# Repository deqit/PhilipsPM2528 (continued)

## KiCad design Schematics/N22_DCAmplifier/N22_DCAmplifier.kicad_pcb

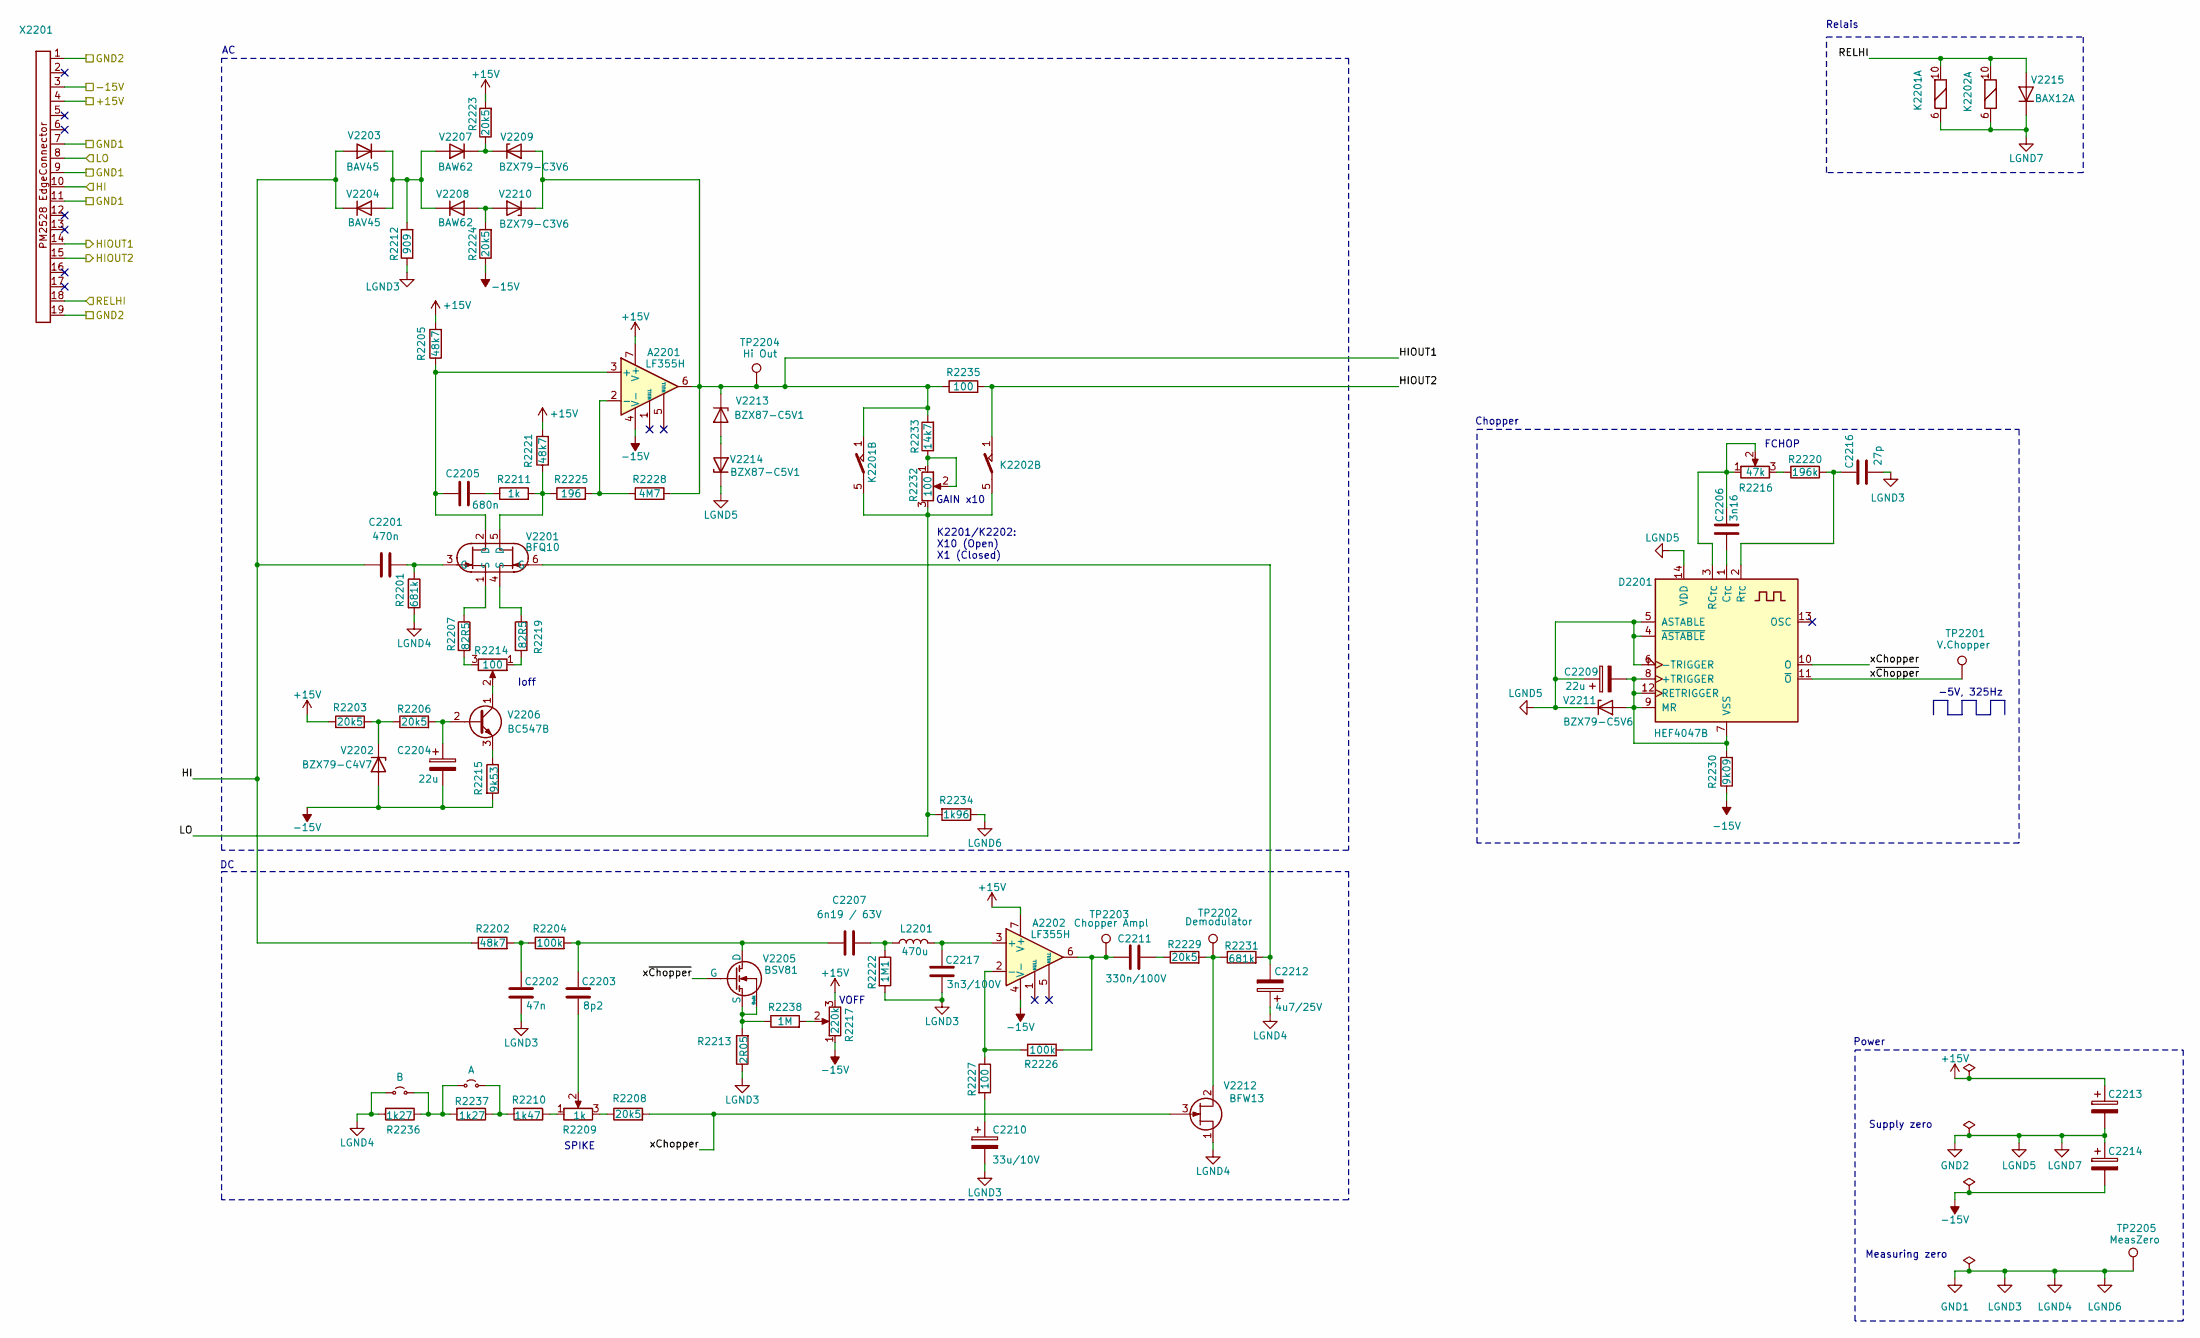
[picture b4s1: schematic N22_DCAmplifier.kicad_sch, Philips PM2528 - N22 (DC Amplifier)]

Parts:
A2201, A2202: LF355H; DIP-8_W7.62mm
C2201: 470n; C_Rect_L18.0mm_W6.0mm_P15.00mm_FKS3_FKP3
C2202: 47n; C_Rect_L10.0mm_W4.0mm_P7.50mm_FKS3_FKP3
C2203: 8p2; C_Disc_D4.3mm_W1.9mm_P5.00mm
C2204, C2209: 22u; CP_Radial_Tantal_D4.5mm_P5.00mm
C2205: 680n; C_Rect_L18.0mm_W5.0mm_P15.00mm_FKS3_FKP3
C2206: 3n16; C_Axial_L3.8mm_D2.6mm_P15.00mm_Horizontal
C2207: 6n19 / 63V; C_Axial_L3.8mm_D2.6mm_P15.00mm_Horizontal
C2210: 33u/10V; CP_Radial_Tantal_D4.5mm_P5.00mm
C2211: 330n/100V; C_Rect_L18.0mm_W5.0mm_P15.00mm_FKS3_FKP3
C2212: 4u7/25V; CP_Radial_Tantal_D4.5mm_P5.00mm
C2213, C2214: 6u8; CP_Radial_Tantal_D4.5mm_P5.00mm
C2216: 27p; C_Disc_D5.1mm_W3.2mm_P5.00mm
C2217: 3n3/100V; C_Disc_D4.3mm_W1.9mm_P5.00mm
D2201: HEF4047B; DIP-14_W7.62mm
JP2201: A; TestPoint_Bridge_Pitch5.08mm_Drill0.7mm
JP2202: B; TestPoint_Bridge_Pitch5.08mm_Drill0.7mm
K2201, K2202: Reed relay assy
L2201: 470u; L_Axial_L9.5mm_D4.0mm_P15.24mm_Horizontal_Fastron_SMCC
R2201, R2231: 681k; R_Axial_DIN0207_L6.3mm_D2.5mm_P10.16mm_Horizontal
R2202, R2205, R2221: 48k7; R_Axial_DIN0207_L6.3mm_D2.5mm_P10.16mm_Horizontal
R2203, R2206, R2208, R2223, R2224, R2229: 20k5; R_Axial_DIN0207_L6.3mm_D2.5mm_P10.16mm_Horizontal
R2204, R2226: 100k; R_Axial_DIN0207_L6.3mm_D2.5mm_P10.16mm_Horizontal
R2207, R2219: 82R5; R_Axial_DIN0207_L6.3mm_D2.5mm_P10.16mm_Horizontal
R2209: 1k; Trimmer vertical
R2210: 1k47; R_Axial_DIN0207_L6.3mm_D2.5mm_P10.16mm_Horizontal
R2211: 1k; R_Axial_DIN0207_L6.3mm_D2.5mm_P10.16mm_Horizontal
R2212: 909; R_Axial_DIN0207_L6.3mm_D2.5mm_P10.16mm_Horizontal
R2213: 2R05; R_Axial_DIN0207_L6.3mm_D2.5mm_P10.16mm_Horizontal
R2214, R2232: 100; Trimmer vertical
R2215: 9k53; R_Axial_DIN0207_L6.3mm_D2.5mm_P10.16mm_Horizontal
R2216: 47k; Trimmer vertical
R2217: 220k; Trimmer vertical
R2220: 196k; R_Axial_DIN0207_L6.3mm_D2.5mm_P10.16mm_Horizontal
R2222: 1M1; R_Axial_DIN0207_L6.3mm_D2.5mm_P10.16mm_Horizontal
R2225: 196; R_Axial_DIN0207_L6.3mm_D2.5mm_P10.16mm_Horizontal
R2227, R2235: 100; R_Axial_DIN0207_L6.3mm_D2.5mm_P10.16mm_Horizontal
R2228: 4M7; R_Axial_DIN0207_L6.3mm_D2.5mm_P10.16mm_Horizontal
R2230: 9k09; R_Axial_DIN0207_L6.3mm_D2.5mm_P10.16mm_Horizontal
R2233: 14k7; R_Axial_DIN0207_L6.3mm_D2.5mm_P10.16mm_Horizontal
R2234: 1k96; R_Axial_DIN0207_L6.3mm_D2.5mm_P10.16mm_Horizontal
R2236, R2237: 1k27; R_Axial_DIN0207_L6.3mm_D2.5mm_P10.16mm_Horizontal
R2238: 1M; R_Axial_DIN0309_L9.0mm_D3.2mm_P15.24mm_Horizontal
TP2201: V.Chopper; Pin_D0.9mm_L10.0mm_W2.4mm_FlatFork
TP2202: Demodulator; Pin_D0.9mm_L10.0mm_W2.4mm_FlatFork
TP2203: Chopper Ampl; Pin_D0.9mm_L10.0mm_W2.4mm_FlatFork
TP2204: Hi Out; Pin_D0.9mm_L10.0mm_W2.4mm_FlatFork
TP2205: MeasZero; Pin_D0.9mm_L10.0mm_W2.4mm_FlatFork
V2201: BFQ10; TO-75-6
V2202: BZX79-C4V7; D_DO-35_SOD27_P10.16mm_Horizontal
V2203, V2204: BAV45; BAV45_TO-18-2
V2205: BSV81; TO-72-4
V2206: BC547B; TO-92_Inline
V2207, V2208: BAW62; D_DO-35_SOD27_P10.16mm_Horizontal
V2209, V2210: BZX79-C3V6; D_DO-35_SOD27_P10.16mm_Horizontal
V2211: BZX79-C5V6; D_DO-35_SOD27_P10.16mm_Horizontal
V2212: BFW13; TO-72-4
V2213, V2214: BZX87-C5V1; D_DO-35_SOD27_P12.70mm_Horizontal
V2215: BAX12A; D_DO-34_SOD68_P10.16mm_Horizontal
X2201: PM2528Edgeconnector

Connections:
+15V: A2201.7 (V+), A2202.7 (V+), C2213.1, R2203.1, R2205.2, R2217.3, R2221.2, R2223.2, X2201.4
-15V: A2201.4 (V-), A2202.4 (V-), C2204.2, C2214.2, R2215.2, R2217.1, R2224.1, R2230.1, V2202.2 (A), X2201.3
/HI: C2201.1, R2202.1, V2203.2 (A), V2204.1 (K), X2201.10
/HIOUT1: A2201.6, K2201.1, R2228.2, R2233.2, R2235.1, TP2204.1 (1_1), V2209.2 (A), V2210.1 (K), V2213.1 (K), X2201.14
/HIOUT2: K2202.1, R2235.2, X2201.15
/LO: K2201.5, K2202.5, R2232.3, R2234.2, X2201.8
/RELHI: K2201.10, K2202.10, V2215.2 (A), X2201.18
/xChopper: D2201.10 (O), R2208.2, V2212.3 (G)
/x~Chopper: D2201.11 (~O), TP2201.1 (1_1), V2205.2 (G)
GND1: C2202.1, C2210.2, C2212.1, C2216.2, C2217.1, JP2202.1 (A_1), R2201.2, R2212.1, R2213.1, R2222.2, R2234.1, R2236.2, TP2205.1 (1_1), V2212.1 (S), X2201.7, X2201.9, X2201.11
GND2: C2209.1, C2213.2, C2214.1, D2201.4 (~ASTABLE), D2201.5 (ASTABLE), D2201.6 (-TRIGGER), D2201.14 (VDD), K2201.6, K2202.6, V2211.1 (K), V2214.1 (K), V2215.1 (K), X2201.1, X2201.19
unnamed: A2201.3 (+), C2205.1, R2205.1, V2201.2 (D)
unnamed: A2201.2 (-), R2225.2, R2228.1
unnamed: A2202.3 (+), C2217.2, L2201.2
unnamed: A2202.2 (-), R2226.1, R2227.1
unnamed: A2202.6, C2211.1, R2226.2, TP2203.1 (1_1)
unnamed: C2201.2, R2201.1, V2201.3 (G)
unnamed: C2202.2, R2202.2, R2204.1
unnamed: C2203.1, R2209.2
unnamed: C2205.2, R2211.1
unnamed: C2207.2, L2201.1, R2222.1
unnamed: C2210.1, R2227.2
unnamed: C2211.2, R2229.1
unnamed: C2212.2, R2231.2, V2201.6 (G)
unnamed: C2209.2, D2201.7 (VSS), D2201.8 (+TRIGGER), D2201.9 (MR), D2201.12 (RETRIGGER), R2230.2, V2211.2 (A)
unnamed: C2206.1, D2201.1 (C_{TC})
unnamed: C2206.2, D2201.3 (RC_{TC}), R2216.1, R2216.2
unnamed: C2216.1, D2201.2 (R_{TC}), R2220.1
unnamed: JP2201.1 (A_1), JP2202.2 (B), R2236.1, R2237.2
unnamed: JP2201.2 (B), R2210.2, R2237.1
unnamed: R2207.1, V2201.1 (S)
unnamed: R2207.2, R2214.3
unnamed: R2208.1, R2209.3
unnamed: R2209.1, R2210.1
unnamed: R2211.2, R2221.1, R2225.1, V2201.5 (D)
unnamed: R2214.1, R2219.2
unnamed: R2216.3, R2220.2
unnamed: R2217.2, R2238.2
unnamed: R2219.1, V2201.4 (S)
unnamed: R2232.1, R2232.2, R2233.1
unnamed: R2203.2, R2206.1, V2202.1 (K)
unnamed: R2212.2, V2203.1 (K), V2204.2 (A), V2207.2 (A), V2208.1 (K)
unnamed: R2213.2, R2238.1, V2205.3 (S), V2205.4 (Bulk)
unnamed: C2203.2, C2207.1, R2204.2, V2205.1 (D)
unnamed: C2204.1, R2206.2, V2206.2 (B)
unnamed: R2214.2, V2206.1 (C)
unnamed: R2215.1, V2206.3 (E)
unnamed: R2223.1, V2207.1 (K), V2209.1 (K)
unnamed: R2224.2, V2208.2 (A), V2210.2 (A)
unnamed: R2229.2, R2231.1, TP2202.1 (1_1), V2212.2 (D)
unnamed: V2213.2 (A), V2214.2 (A)

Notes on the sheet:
Relais
SPIKE
Supply zero
GAIN x10
K2201/K2202: X10 (Open) X1 (Closed)
VOFF
Chopper
-5V, 325Hz
FCHOP
Power
Measuring zero
Ioff

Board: 2 copper layers, 81 parts (0 on the bottom side), 51 nets, no tracks yet.

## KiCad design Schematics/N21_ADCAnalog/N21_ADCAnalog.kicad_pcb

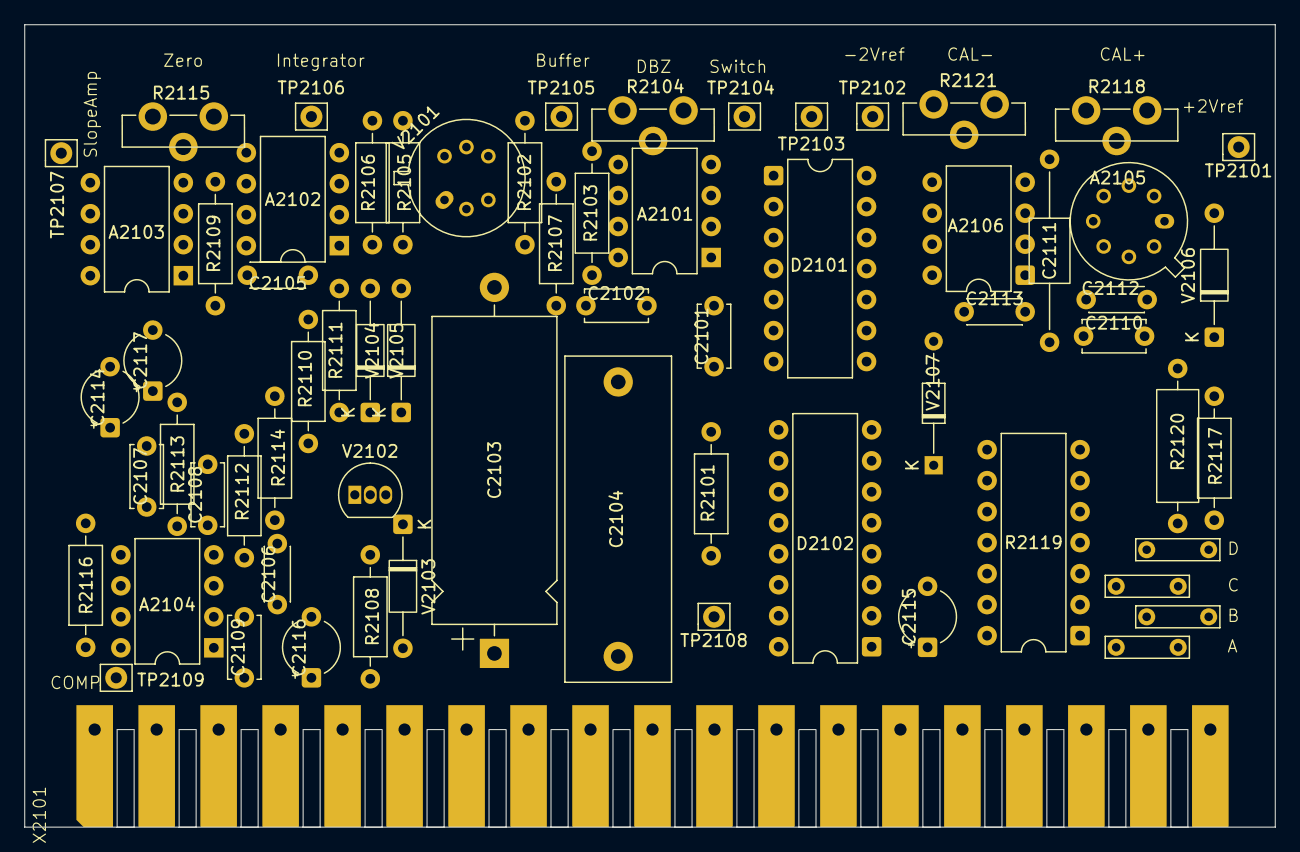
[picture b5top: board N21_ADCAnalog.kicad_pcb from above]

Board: 2 copper layers, 102.5 x 65.8 mm, 67 parts (0 on the bottom side), 54 nets, no tracks yet.

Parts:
A2101: LF356H; DIP-8_W7.62mm
A2102, A2106: LM201AN; DIP-8_W7.62mm
A2103: LF355H; DIP-8_W7.62mm
A2104: LM311N; DIP-8_W7.62mm
A2105: LM208AH; TO-99-8
C2101, C2102: 10n; C_Disc_D5.0mm_W2.5mm_P5.00mm
C2103: 162n; CP_Axial_L25.0mm_D10.0mm_P30.00mm_Horizontal
C2104: 3u3; C_Rect_L26.5mm_W8.5mm_P22.50mm_MKS4
C2105: 33p/100V; C_Disc_D4.3mm_W1.9mm_P5.00mm
C2106: 220p/500V; C_Disc_D4.3mm_W1.9mm_P5.00mm
C2107, C2108, C2109: 22n; C_Disc_D5.0mm_W2.5mm_P5.00mm
C2110: 4n7; C_Disc_D5.0mm_W2.5mm_P5.00mm
C2111: 4n22; C_Axial_L5.1mm_D3.1mm_P15.00mm_Horizontal
C2112, C2113: 33p; C_Disc_D4.3mm_W1.9mm_P5.00mm
C2114, C2117: 6u8; CP_Radial_Tantal_D4.5mm_P5.00mm
C2115: 22u/10V; CP_Radial_Tantal_D4.5mm_P5.00mm
C2116: 22u; CP_Radial_Tantal_D4.5mm_P5.00mm
D2101: HEF4066B; DIP-14_W7.62mm
D2102: HEF4104B; DIP-16_W7.62mm
JP2101: A; TestPoint_Bridge_Pitch5.08mm_Drill0.7mm
JP2102: B; TestPoint_Bridge_Pitch5.08mm_Drill0.7mm
JP2103: C; TestPoint_Bridge_Pitch5.08mm_Drill0.7mm
JP2104: D; TestPoint_Bridge_Pitch5.08mm_Drill0.7mm
R2101: 8k66; R_Axial_DIN0207_L6.3mm_D2.5mm_P10.16mm_Horizontal
R2102: 140k; R_Axial_DIN0207_L6.3mm_D2.5mm_P10.16mm_Horizontal
R2103: 64k9; R_Axial_DIN0207_L6.3mm_D2.5mm_P10.16mm_Horizontal
R2104: 680k; Trimmer vertical
R2105, R2106: 21M1; R_Axial_DIN0207_L6.3mm_D2.5mm_P10.16mm_Horizontal
R2107: 24k9; R_Axial_DIN0207_L6.3mm_D2.5mm_P10.16mm_Horizontal
R2108: 40k2; R_Axial_DIN0207_L6.3mm_D2.5mm_P10.16mm_Horizontal
R2109: 5k9; R_Axial_DIN0207_L6.3mm_D2.5mm_P10.16mm_Horizontal
R2110: 121k; R_Axial_DIN0207_L6.3mm_D2.5mm_P10.16mm_Horizontal
R2111: 5k90; R_Axial_DIN0207_L6.3mm_D2.5mm_P10.16mm_Horizontal
R2112, R2113: 442; R_Axial_DIN0207_L6.3mm_D2.5mm_P10.16mm_Horizontal
R2114: 442k; R_Axial_DIN0207_L6.3mm_D2.5mm_P10.16mm_Horizontal
R2115: 47k; Trimmer vertical
R2116: 1k05; R_Axial_DIN0207_L6.3mm_D2.5mm_P10.16mm_Horizontal
R2117: 8k25; R_Axial_DIN0207_L6.3mm_D2.5mm_P10.16mm_Horizontal
R2118: 33; Trimmer vertical
R2119: OM528; DIP-14_W7.62mm
R2120: 590; R_Axial_DIN0309_L9.0mm_D3.2mm_P12.70mm_Horizontal
R2121: 100; Trimmer vertical
TP2101: +2Vref; Pin_D0.9mm_L10.0mm_W2.4mm_FlatFork
TP2102: -2Vref; Pin_D0.9mm_L10.0mm_W2.4mm_FlatFork
TP2103: 0Vref; Pin_D0.9mm_L10.0mm_W2.4mm_FlatFork
TP2104: Switch; Pin_D0.9mm_L10.0mm_W2.4mm_FlatFork
TP2105: Buffer; Pin_D0.9mm_L10.0mm_W2.4mm_FlatFork
TP2106: Integrator; Pin_D0.9mm_L10.0mm_W2.4mm_FlatFork
TP2107: Slope Amp; Pin_D0.9mm_L10.0mm_W2.4mm_FlatFork
TP2108: Input; Pin_D0.9mm_L10.0mm_W2.4mm_FlatFork
TP2109: Comp; Pin_D0.9mm_L10.0mm_W2.4mm_FlatFork
V2101: ON528; TO-75-6
V2102: BSV80; TO-92_Inline
V2103, V2104, V2105, V2106: BAW62; D_DO-35_SOD27_P10.16mm_Horizontal
V2107: BZV14; D_DO-34_SOD68_P10.16mm_Horizontal
X2101: PM2528Edgeconnector

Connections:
+5V: C2115.1, D2101.14 (VDD), D2102.1 (VDDO), X2101.5
+15V: A2101.7 (V+), A2102.7 (V+), A2103.7 (V+), A2104.8 (V+), A2105.7 (V+), A2106.7 (V+), C2101.2, C2107.1, C2114.1, R2107.1, R2115.1, R2117.2, X2101.4
-5V: A2104.1 (GND), C2109.2, C2116.2, D2101.7 (VSS), D2102.8 (VSS), X2101.2
-15V: A2101.4 (V-), A2102.4 (V-), A2103.4 (V-), A2104.4 (V-), A2105.4 (V-), A2106.4 (V-), C2102.2, C2108.2, C2117.2, R2105.2, R2106.2, R2115.3, X2101.3
/+2VRef: C2110.2, D2101.11 (Y3), R2117.1, R2118.2, R2118.3, R2119.8, TP2101.1 (1_1), V2106.1 (K), X2101.7
/AZ: D2102.5 (I1), X2101.12
/COMP: A2104.7, R2116.2, TP2109.1 (1_1), X2101.19
/DN+: D2102.12 (I3), X2101.13
/DN-: D2102.4 (I0), X2101.11
/INPUT: R2101.1, TP2108.1 (1_1), X2101.9
/UP: D2102.11 (I2), X2101.14
/xAZ: D2101.5 (E1), D2102.6 (O1), V2103.1 (K)
/xDN+: D2101.12 (E3), D2102.13 (O3)
/xDN-: D2101.6 (E2), D2102.3 (O0)
/xUP: D2101.13 (E0), D2102.10 (O2)
GND1: A2103.3 (+), C2104.2, C2110.1, C2111.2, D2101.4 (Y1), D2102.15 (EO), D2102.16 (VDDI), R2113.2, R2119.10, TP2103.1 (1_1), X2101.6, X2101.8, X2101.10
GND2: C2101.1, C2102.1, C2107.2, C2108.1, C2109.1, C2114.2, C2115.2, C2116.1, C2117.1, R2108.2, R2116.1, V2104.1 (K), V2105.2 (A), X2101.1, X2101.18
unnamed: A2101.3 (+), D2101.2 (Z0), D2101.3 (Z1), D2101.9 (Z2), D2101.10 (Z3), TP2104.1 (1_1)
unnamed: A2101.2 (-), A2101.6, R2102.2, R2103.2, TP2105.1 (1_1)
unnamed: A2102.3 (+), R2106.1, V2101.4 (S)
unnamed: A2102.2 (-), R2105.1, V2101.1 (S)
unnamed: A2102.1 (BAL), C2105.1
unnamed: A2102.8 (C/B), C2105.2
unnamed: A2102.6, C2103.1, R2109.1, TP2106.1 (1_1)
unnamed: A2103.2 (-), R2109.2, R2110.1
unnamed: A2103.6, R2110.2, R2111.2, R2112.1, TP2107.1 (1_1)
unnamed: A2104.2 (+), C2106.2, R2104.1, R2104.2, R2113.1, R2114.1
unnamed: A2104.3 (-), C2106.1, R2112.2
unnamed: A2104.5 (BAL), A2104.6 (STRB)
unnamed: A2105.3 (+), R2119.6
unnamed: A2105.2 (-), A2106.2 (-), R2119.4
unnamed: A2105.1 (BAL), C2112.1
unnamed: A2105.8 (C/B), C2112.2
unnamed: A2106.3 (+), R2119.9
unnamed: A2106.1 (BAL), C2113.2
unnamed: A2106.8 (C/B), C2113.1
unnamed: C2103.2, R2102.1, V2101.3 (G)
unnamed: D2101.1 (Y0), R2101.2
unnamed: C2111.1, D2101.8 (Y2), R2119.12, TP2102.1 (1_1)
unnamed: JP2101.1 (A_1), JP2102.1 (A_1), R2119.14
unnamed: R2119.1, R2120.1
unnamed: JP2103.1 (A_1), R2119.2
unnamed: JP2104.1 (A_1), R2119.11
unnamed: R2118.1, R2119.5
unnamed: R2103.1, R2104.3
unnamed: R2107.2, V2101.2 (D), V2101.5 (D)
unnamed: R2114.2, R2115.2
unnamed: R2120.2, R2121.3
unnamed: R2111.1, V2102.1 (D), V2104.2 (A), V2105.1 (K)
unnamed: R2108.1, V2102.2 (G), V2103.2 (A)
unnamed: C2104.1, V2101.6 (G), V2102.3 (S)
unnamed: A2105.6, V2106.2 (A)
unnamed: A2106.6, R2121.1, R2121.2, V2107.2 (A)
unnamed: R2119.7, V2107.1 (K)

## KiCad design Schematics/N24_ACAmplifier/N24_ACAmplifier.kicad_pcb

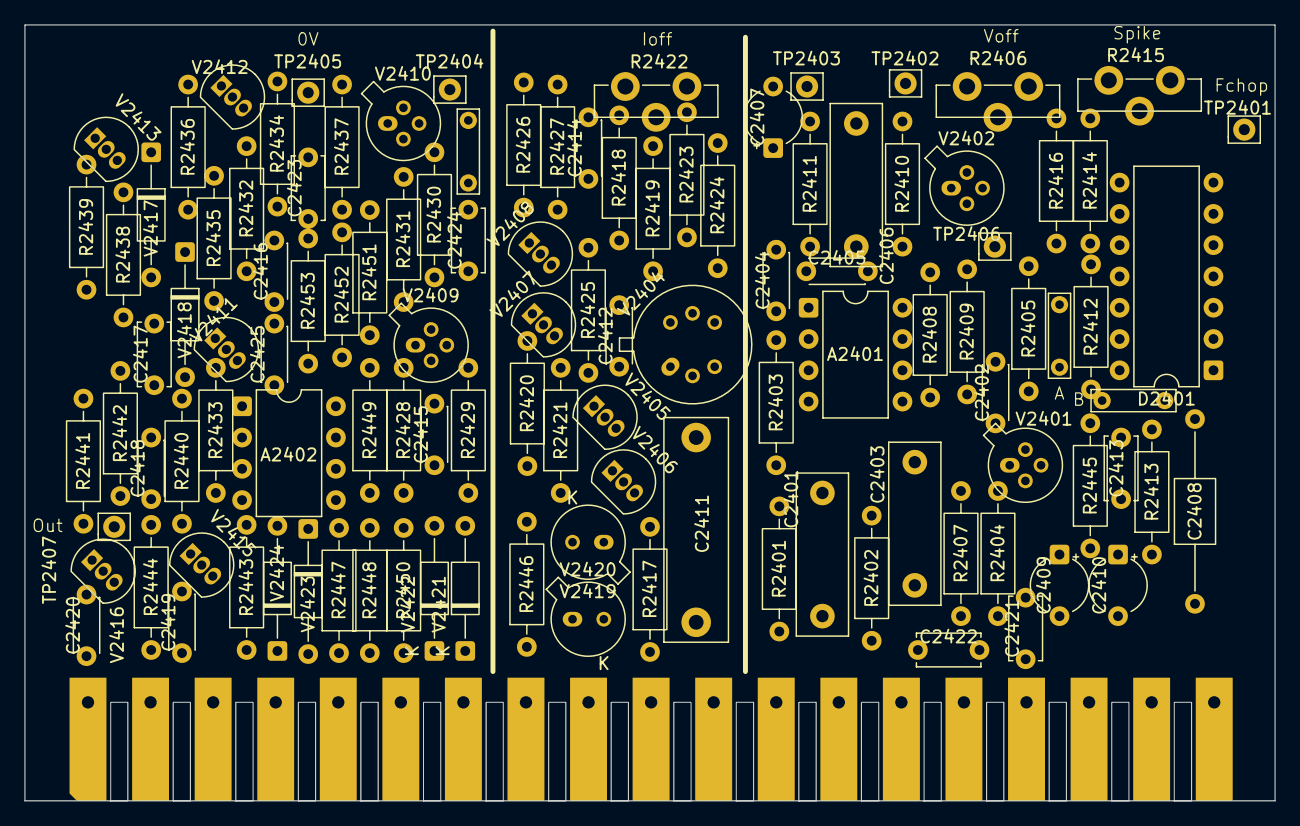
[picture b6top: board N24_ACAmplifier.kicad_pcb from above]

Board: 2 copper layers, 101.5 x 63.0 mm, 114 parts (0 on the bottom side), 66 nets, no tracks yet.

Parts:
A2401: LM308AN; DIP-8_W7.62mm
A2402: LM393N; DIP-8_W7.62mm
C2401: 22n; C_Rect_L13.0mm_W4.0mm_P10.00mm_FKS3_FKP3_MKS4
C2402: 8p2; C_Disc_D4.3mm_W1.9mm_P5.00mm
C2403: 33n; C_Rect_L13.0mm_W4.0mm_P10.00mm_FKS3_FKP3_MKS4
C2404: 220p; C_Disc_D4.3mm_W1.9mm_P5.00mm
C2405: 3p9; C_Disc_D4.3mm_W1.9mm_P5.00mm
C2406: 220n; C_Rect_L13.0mm_W4.0mm_P10.00mm_FKS3_FKP3_MKS4
C2407: 22u; CP_Radial_Tantal_D4.5mm_P5.00mm
C2408: 13n3; C_Axial_L5.1mm_D3.1mm_P15.00mm_Horizontal
C2409, C2410: 6u8; CP_Radial_Tantal_D4.5mm_P5.00mm
C2411: 330n; C_Rect_L18.0mm_W5.0mm_P15.00mm_FKS3_FKP3
C2412: 150p; C_Disc_D4.3mm_W1.9mm_P5.00mm
C2413, C2417: 10n; C_Disc_D5.0mm_W2.5mm_P5.00mm
C2414: 1n8; C_Disc_D4.3mm_W1.9mm_P5.00mm
C2415: 15p; C_Disc_D4.3mm_W1.9mm_P5.00mm
C2416: 12p; C_Disc_D4.3mm_W1.9mm_P5.00mm
C2418: 560p; C_Disc_D4.3mm_W1.9mm_P5.00mm
C2419, C2420: 6n8; C_Disc_D4.3mm_W1.9mm_P5.00mm
C2421, C2422, C2423, C2424: 22n; C_Disc_D5.0mm_W2.5mm_P5.00mm
C2425: 39p; C_Disc_D4.3mm_W1.9mm_P5.00mm
D2401: HEF4047B; DIP-14_W7.62mm
JP1: Jumper_2_Small_Bridged; TestPoint_Bridge_Pitch5.08mm_Drill0.7mm
JP2401: A; TestPoint_Bridge_Pitch5.08mm_Drill0.7mm
JP2402: B; TestPoint_Bridge_Pitch5.08mm_Drill0.7mm
R2401, R2407, R2411: 1M; R_Axial_DIN0207_L6.3mm_D2.5mm_P10.16mm_Horizontal
R2402: 95k3; R_Axial_DIN0207_L6.3mm_D2.5mm_P10.16mm_Horizontal
R2403: 9k53; R_Axial_DIN0207_L6.3mm_D2.5mm_P10.16mm_Horizontal
R2404: 15R4; R_Axial_DIN0207_L6.3mm_D2.5mm_P10.16mm_Horizontal
R2405, R2408: 681k; R_Axial_DIN0207_L6.3mm_D2.5mm_P10.16mm_Horizontal
R2406: 220k; Trimmer vertical
R2409, R2425: 2k74; R_Axial_DIN0207_L6.3mm_D2.5mm_P10.16mm_Horizontal
R2410, R2448: 15k4; R_Axial_DIN0207_L6.3mm_D2.5mm_P10.16mm_Horizontal
R2412, R2445, R2451, R2452: 1k05; R_Axial_DIN0207_L6.3mm_D2.5mm_P10.16mm_Horizontal
R2413: 634k; R_Axial_DIN0207_L6.3mm_D2.5mm_P10.16mm_Horizontal
R2414: 17k8; R_Axial_DIN0207_L6.3mm_D2.5mm_P10.16mm_Horizontal
R2415: 1k; Trimmer vertical
R2416, R2446: 1k21; R_Axial_DIN0207_L6.3mm_D2.5mm_P10.16mm_Horizontal
R2417, R2428: 10M; R_Axial_DIN0207_L6.3mm_D2.5mm_P10.16mm_Horizontal
R2418, R2419, R2423, R2449: 46k4; R_Axial_DIN0207_L6.3mm_D2.5mm_P10.16mm_Horizontal
R2420, R2421: 8k25; R_Axial_DIN0207_L6.3mm_D2.5mm_P10.16mm_Horizontal
R2422: 150; Trimmer vertical
R2424: 10k; R_Axial_DIN0207_L6.3mm_D2.5mm_P10.16mm_Horizontal
R2426: 1k78; R_Axial_DIN0207_L6.3mm_D2.5mm_P10.16mm_Horizontal
R2427: 140; R_Axial_DIN0207_L6.3mm_D2.5mm_P10.16mm_Horizontal
R2429: 301k; R_Axial_DIN0207_L6.3mm_D2.5mm_P10.16mm_Horizontal
R2430: 60k4; R_Axial_DIN0207_L6.3mm_D2.5mm_P10.16mm_Horizontal
R2431, R2437: 2k15; R_Axial_DIN0207_L6.3mm_D2.5mm_P10.16mm_Horizontal
R2432: 205; R_Axial_DIN0207_L6.3mm_D2.5mm_P10.16mm_Horizontal
R2433: 2k61; R_Axial_DIN0207_L6.3mm_D2.5mm_P10.16mm_Horizontal
R2434: 2k37; R_Axial_DIN0207_L6.3mm_D2.5mm_P10.16mm_Horizontal
R2435, R2436: 7R5; R_Axial_DIN0207_L6.3mm_D2.5mm_P10.16mm_Horizontal
R2438: 4k64; R_Axial_DIN0207_L6.3mm_D2.5mm_P10.16mm_Horizontal
R2439: 215; R_Axial_DIN0207_L6.3mm_D2.5mm_P10.16mm_Horizontal
R2440, R2441, R2443, R2444: 71R5; R_Axial_DIN0207_L6.3mm_D2.5mm_P10.16mm_Horizontal
R2442: 2R15; R_Axial_DIN0207_L6.3mm_D2.5mm_P10.16mm_Horizontal
R2447: 15K4; R_Axial_DIN0207_L6.3mm_D2.5mm_P10.16mm_Horizontal
R2450, R2453: 30k1; R_Axial_DIN0207_L6.3mm_D2.5mm_P10.16mm_Horizontal
TP2401: Fchop; Pin_D0.9mm_L10.0mm_W2.4mm_FlatFork
TP2402: Demod; Pin_D0.9mm_L10.0mm_W2.4mm_FlatFork
TP2403: OffsetCorr; Pin_D0.9mm_L10.0mm_W2.4mm_FlatFork
TP2404: DriverBias; Pin_D0.9mm_L10.0mm_W2.4mm_FlatFork
TP2405: 0V; Pin_D0.9mm_L10.0mm_W2.4mm_FlatFork
TP2406: ChopperAmpl; Pin_D0.9mm_L10.0mm_W2.4mm_FlatFork
TP2407: AC OUT; Pin_D0.9mm_L10.0mm_W2.4mm_FlatFork
V2401: BSV81; TO-72-4
V2402: BFW13; TO-72-4
V2404: BFQ14; TO-75-6
V2405, V2406, V2413: BC547B; TO-92_Inline
V2407, V2408: BC557B; TO-92_Inline
V2409, V2410: BFW11; TO-72-4
V2411, V2412, V2415: BF199; TO-92_Inline
V2416: BF324; TO-92_Inline
V2417: BZX79-C3V0; D_DO-35_SOD27_P10.16mm_Horizontal
V2418: BZX46-C2V0; D_DO-35_SOD27_P10.16mm_Horizontal
V2419, V2420: BAV45; BAV45_TO-18-2
V2421, V2422: BAW62; D_DO-35_SOD27_P10.16mm_Horizontal
V2423, V2424: BZX79-B8V2; D_DO-35_SOD27_P10.16mm_Horizontal
X2401: PM2528Edgeconnector

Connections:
+15V: A2401.7 (V+), A2402.8 (V+), C2409.1, C2419.2, C2421.1, C2423.1, R2406.1, R2418.2, R2419.2, R2425.2, R2433.2, R2434.2, R2447.2, R2453.1, V2405.1 (C), V2406.1 (C), V2415.1 (C), X2401.4
-5V: C2413.1, D2401.7 (VSS), D2401.8 (+TRIGGER), D2401.9 (MR), D2401.12 (RETRIGGER), X2401.2
-15V: A2401.4 (V-), A2402.4 (V-), C2410.2, C2420.1, C2422.2, C2424.2, C2425.1, R2406.3, R2423.1, R2426.1, R2430.1, R2431.1, R2437.1, R2439.1, R2448.1, R2450.1, V2407.1 (C), V2416.3 (C), V2417.2 (A), X2401.3
/CFI: A2402.1, A2402.7, C2425.2, R2449.2, X2401.14
/IN: C2411.2, R2401.1, V2419.2 (A), V2420.1 (K), X2401.10
/OUT: C2418.1, R2443.1, R2444.2, TP2407.1 (1_1), V2423.2 (A), V2424.1 (K), X2401.17
GND2: C2401.2, C2404.2, C2407.2, C2409.2, C2410.1, C2413.2, C2414.1, C2419.1, C2420.2, C2421.2, C2422.1, C2423.2, C2424.1, D2401.4 (~ASTABLE), D2401.5 (ASTABLE), D2401.6 (-TRIGGER), D2401.14 (VDD), R2404.1, R2407.1, R2409.1, R2417.1, R2420.1, R2421.1, R2429.1, R2438.1, R2445.2, R2446.1, R2449.1, R2451.1, R2452.1, TP2405.1 (1_1), V2402.1 (S), V2409.2 (S), V2410.2 (S), X2401.1, X2401.6, X2401.9, X2401.11, X2401.13, X2401.19
unnamed: A2401.3 (+), C2404.1, R2403.2
unnamed: A2401.2 (-), R2408.1, R2409.2
unnamed: A2401.1 (CompenA), C2405.1
unnamed: A2401.8 (CompenB), C2405.2
unnamed: A2401.6, C2406.1, R2408.2, TP2406.1 (1_1)
unnamed: A2402.3 (+), R2452.2, R2453.2
unnamed: A2402.2 (-), R2448.2, V2422.2 (A), V2424.2 (A)
unnamed: A2402.5 (+), R2447.1, V2421.1 (K), V2423.1 (K)
unnamed: A2402.6 (-), R2450.2, R2451.2
unnamed: C2401.1, R2401.2, R2402.1
unnamed: C2402.1, R2415.2
unnamed: C2403.2, R2403.1, R2407.2
unnamed: C2406.2, R2410.1
unnamed: C2407.1, R2411.2, R2424.1, TP2403.1 (1_1)
unnamed: C2411.1, C2415.1, R2417.2, V2404.3 (G)
unnamed: C2414.2, R2427.1
unnamed: C2416.1, R2432.1
unnamed: C2418.2, R2442.2
unnamed: C2408.2, D2401.1 (C_{TC})
unnamed: D2401.10 (O), R2414.1, TP2401.1 (1_1), V2402.3 (G)
unnamed: C2408.1, D2401.3 (RC_{TC}), R2413.2
unnamed: D2401.2 (R_{TC}), R2413.1
unnamed: D2401.11 (~O), V2401.2 (G)
unnamed: JP1.1 (A_1), R2426.2, R2427.2, V2408.1 (C)
unnamed: TP2404.1 (1_1), V2410.1 (G)
unnamed: JP2401.1 (A_1), R2412.1, R2416.2
unnamed: JP2402.1 (A_1), R2412.2, R2445.1
unnamed: R2405.2, R2406.2
unnamed: R2414.2, R2415.3
unnamed: R2415.1, R2416.1
unnamed: R2422.1, V2404.4 (S)
unnamed: R2422.2, R2423.2
unnamed: R2422.3, V2404.1 (S)
unnamed: R2424.2, V2404.6 (G)
unnamed: R2428.1, R2429.2, R2430.2
unnamed: R2404.2, R2405.1, V2401.3 (S), V2401.4 (Bulk)
unnamed: C2402.2, C2403.1, R2402.2, V2401.1 (D)
unnamed: R2410.2, R2411.1, TP2402.1 (1_1), V2402.2 (D)
unnamed: C2412.2, R2418.1, V2404.2 (D), V2405.2 (B)
unnamed: R2420.2, V2405.3 (E), V2407.2 (B)
unnamed: C2412.1, R2419.1, V2404.5 (D), V2406.2 (B)
unnamed: R2421.2, V2406.3 (E), V2408.2 (B)
unnamed: R2425.1, V2407.3 (E), V2408.3 (E)
unnamed: R2431.2, V2409.3 (D), V2411.3 (B)
unnamed: C2415.2, R2428.2, V2409.1 (G)
unnamed: R2437.2, V2410.3 (D), V2412.3 (B)
unnamed: C2416.2, C2417.1, R2441.1, R2442.1, V2411.1 (C), V2418.1 (K)
unnamed: R2435.1, V2411.2 (E)
unnamed: R2432.2, R2434.1, V2412.1 (C)
unnamed: R2436.2, V2412.2 (E)
unnamed: R2438.2, V2413.2 (B), V2417.1 (K)
unnamed: R2435.2, R2436.1, V2413.1 (C)
unnamed: R2439.2, V2413.3 (E)
unnamed: R2440.2, V2415.3 (B)
unnamed: R2443.2, V2415.2 (E)
unnamed: R2441.2, V2416.2 (B)
unnamed: R2444.1, V2416.1 (E)
unnamed: C2417.2, R2433.1, R2440.1, V2418.2 (A)
unnamed: R2446.2, V2419.1 (K), V2420.2 (A), V2421.2 (A), V2422.1 (K)
